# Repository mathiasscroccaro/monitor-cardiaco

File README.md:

# monitor-cardiaco
Códigos fonte da interface de visualização do sinal, instruções programadas no microcontrolador e também esquemáticos dos circuitos do protótipo de monitor cardíaco

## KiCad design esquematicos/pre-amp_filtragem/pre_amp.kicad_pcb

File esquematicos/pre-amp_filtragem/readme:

Arquivos do esquemático da placa de pré-amplificação e filtragem analógica do protótipo de monitor cardíaco

Os esquemáticos presentes neste diretórios são compatíveis com o software EDA Kicad

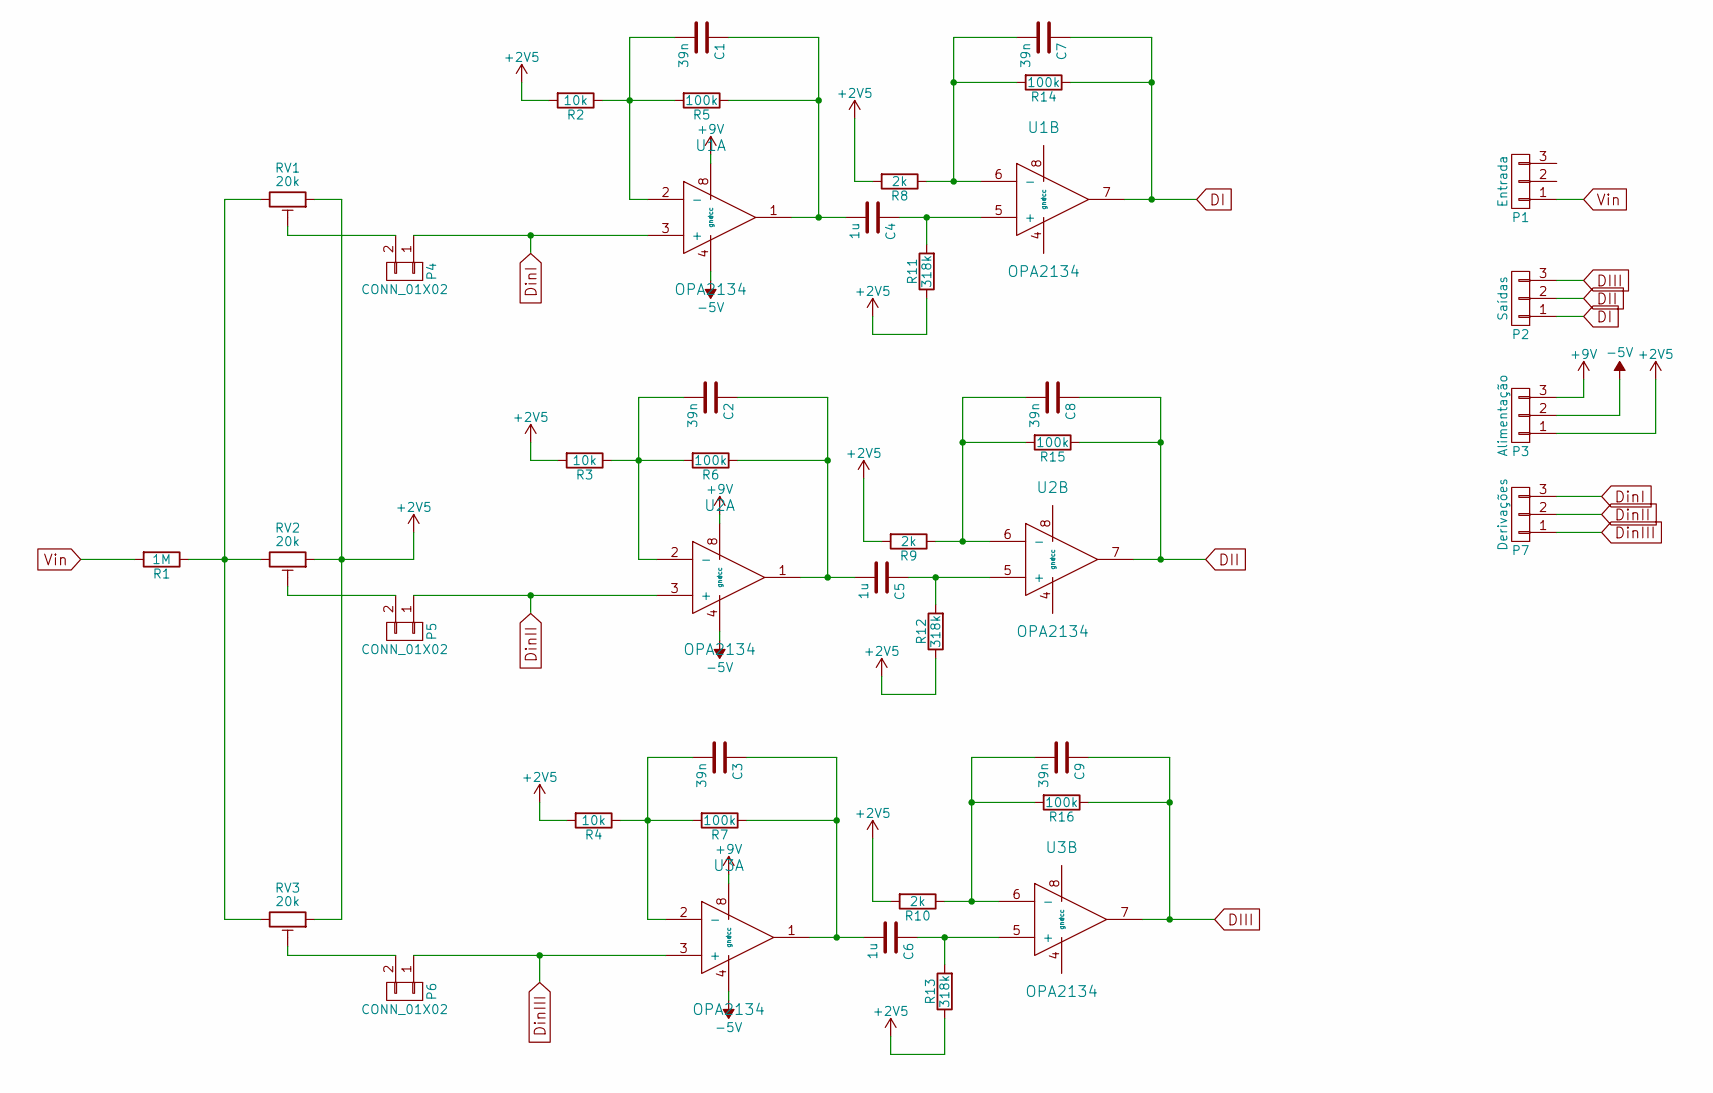
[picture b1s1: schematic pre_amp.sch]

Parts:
C1, C2, C3, C7, C8, C9: 39n; C_Disc_D7.5mm_W4.4mm_P5.00mm
C4, C5, C6: 1u; C_Axial_L12.0mm_D6.5mm_P15.00mm_Horizontal
P1: Entrada; AK300-3
P2: Saídas; AK300-3
P3: Alimentação; AK300-3
P4, P5, P6: CONN_01X02; PINHEAD1-2
P7: Derivações; AK300-3
R1: 1M; R_Axial_DIN0207_L6.3mm_D2.5mm_P10.16mm_Horizontal
R2, R3, R4: 10k; R_Axial_DIN0207_L6.3mm_D2.5mm_P10.16mm_Horizontal
R5, R6, R7, R14, R15, R16: 100k; R_Axial_DIN0207_L6.3mm_D2.5mm_P10.16mm_Horizontal
R8, R9, R10: 2k; R_Axial_DIN0207_L6.3mm_D2.5mm_P10.16mm_Horizontal
R11, R12, R13: 318k; R_Axial_DIN0207_L6.3mm_D2.5mm_P10.16mm_Horizontal
RV1, RV2, RV3: 20k; Potentiometer_Trimmer_Bourns_3296W
U1, U2, U3: OPA2134; DIP-8_W7.62mm_LongPads

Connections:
+2V5: P3.1, R2.2, R3.2, R4.2, R8.2, R9.2, R10.2, R11.1, R12.1, R13.1, RV1.1, RV2.1, RV3.1
+9V: P3.3, U1.8 (vcc), U2.8 (vcc), U3.8 (vcc)
-5V: P3.2, U1.4 (gnd), U2.4 (gnd), U3.4 (gnd)
DI: C7.1, P2.1, R14.1, U1.7
DII: C8.1, P2.2, R15.1, U2.7
DIII: C9.1, P2.3, R16.1, U3.7
DinI: P4.1, P7.3, U1.3 (+)
DinII: P5.1, P7.2, U2.3 (+)
DinIII: P6.1, P7.1, U3.3 (+)
unnamed: C1.1, C4.2, R5.1, U1.1
unnamed: C1.2, R2.1, R5.2, U1.2 (-)
unnamed: C2.1, C5.2, R6.1, U2.1
unnamed: C2.2, R3.1, R6.2, U2.2 (-)
unnamed: C3.1, C6.2, R7.1, U3.1
unnamed: C3.2, R4.1, R7.2, U3.2 (-)
unnamed: C4.1, R11.2, U1.5 (+)
unnamed: C5.1, R12.2, U2.5 (+)
unnamed: C6.1, R13.2, U3.5 (+)
unnamed: C7.2, R8.1, R14.2, U1.6 (-)
unnamed: C8.2, R9.1, R15.2, U2.6 (-)
unnamed: C9.2, R10.1, R16.2, U3.6 (-)
unnamed: P4.2, RV1.2
unnamed: P5.2, RV2.2
unnamed: P6.2, RV3.2
unnamed: R1.1, RV1.3, RV2.3, RV3.3
Vin: P1.1, R1.2

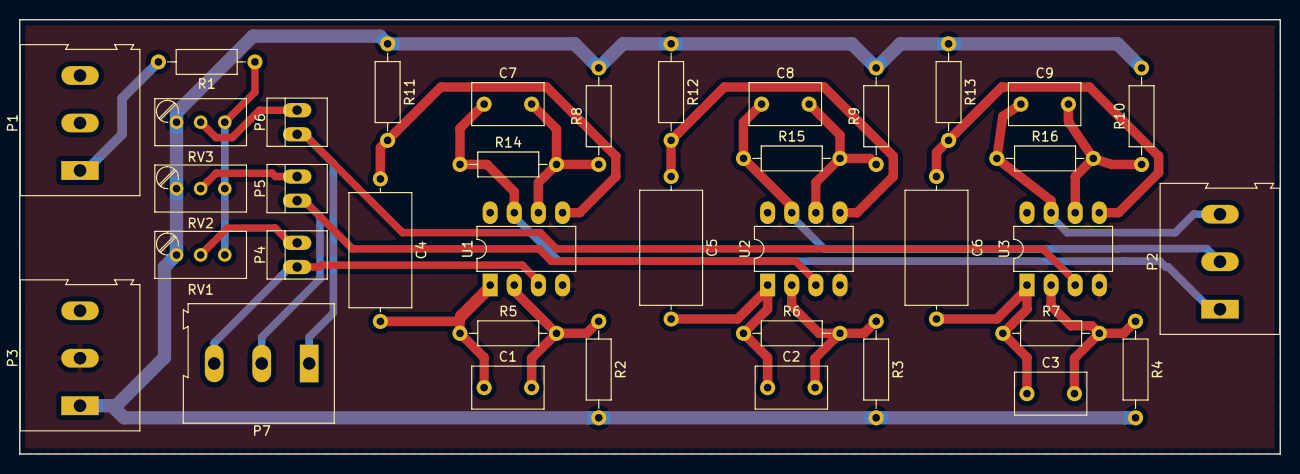
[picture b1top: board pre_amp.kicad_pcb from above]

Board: 2 copper layers, 132.7 x 45.7 mm, 38 parts (0 on the bottom side), 26 nets.
